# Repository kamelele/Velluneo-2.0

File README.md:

# Velluneo-2.0

[Projekt E27 z wymiennym wkładem LED](hardware/E27/README.md)

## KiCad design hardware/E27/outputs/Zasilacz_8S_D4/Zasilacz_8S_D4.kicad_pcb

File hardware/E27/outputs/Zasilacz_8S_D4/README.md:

# Velluneo E27 8S-D4

Open [Zasilacz_8S_D4.kicad_pro](Zasilacz_8S_D4.kicad_pro) in KiCad 10.0.8. This draft adds a hardware inhibit to the 8-LED supply while its 3.3 V logic rail is low. The [70 × 34 mm board](Zasilacz_8S_D4.kicad_pcb) is an unrouted placement study.

- [Schematic](Zasilacz_8S_D4.kicad_sch)
- [3D top](8S-D4-top.png) · [3D bottom](8S-D4-bottom.png)
- [Design decision and evidence](../../workflow/8s/driver-8s-d4-inhibit.md)

Retained fault state after full rail loss, independent insulation checks and routing remain open. The earlier [D3 study](../Zasilacz_8S_Draft/README.md) is available as a baseline.

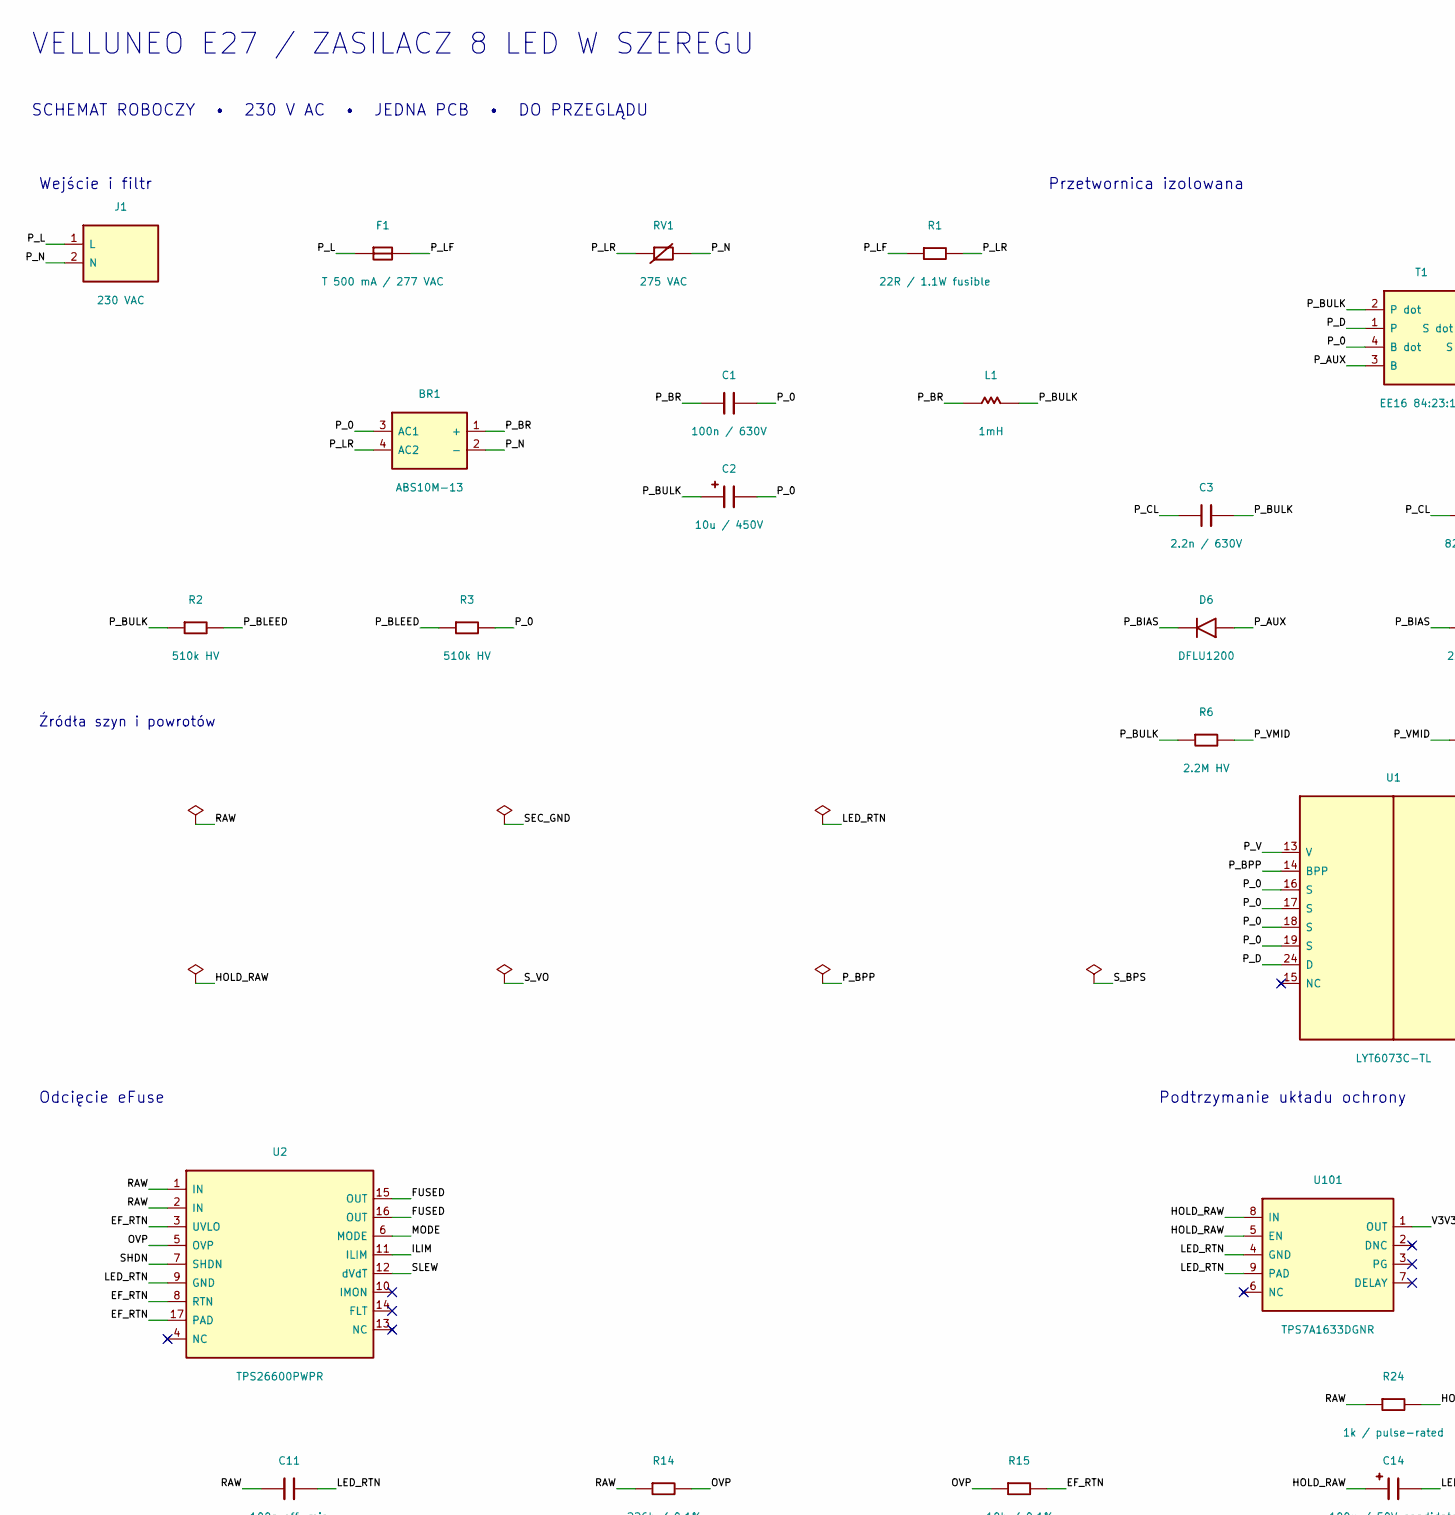
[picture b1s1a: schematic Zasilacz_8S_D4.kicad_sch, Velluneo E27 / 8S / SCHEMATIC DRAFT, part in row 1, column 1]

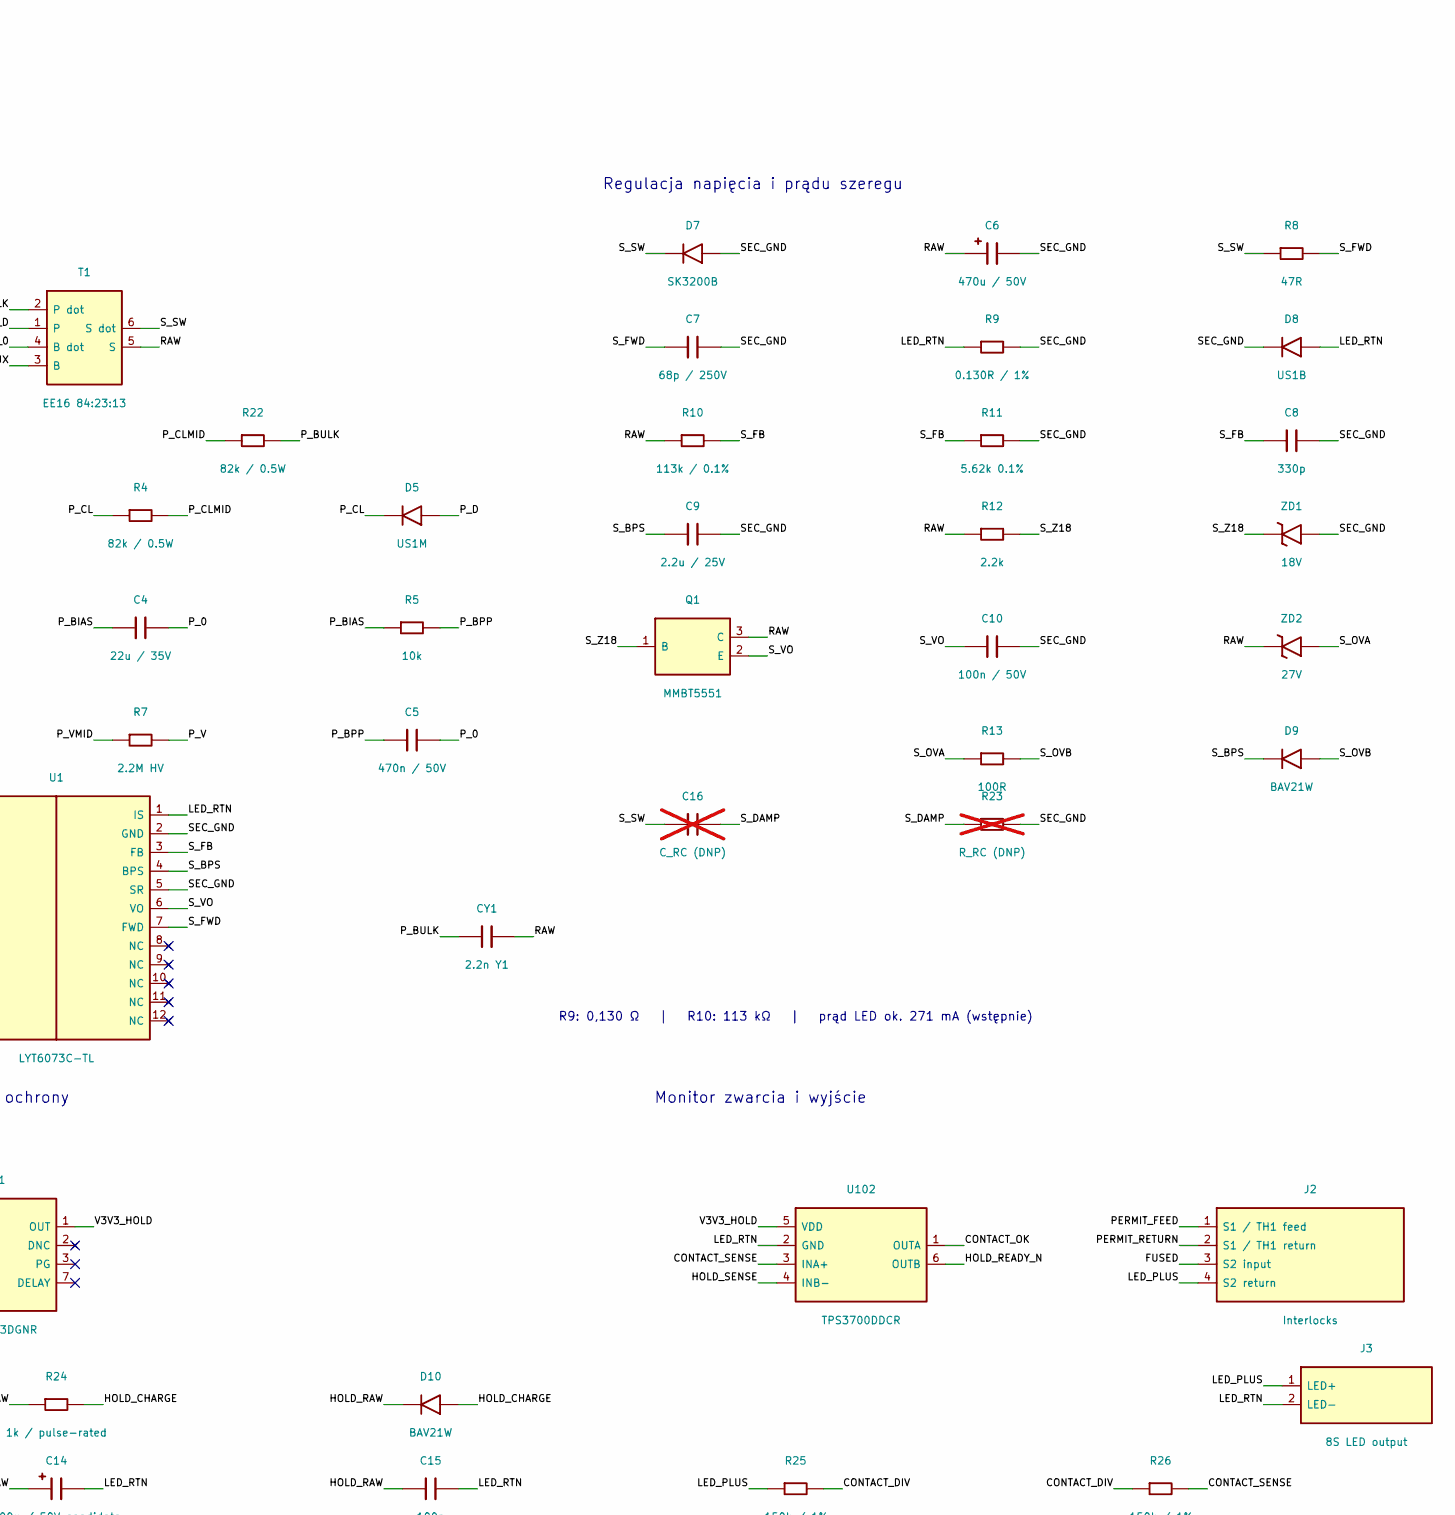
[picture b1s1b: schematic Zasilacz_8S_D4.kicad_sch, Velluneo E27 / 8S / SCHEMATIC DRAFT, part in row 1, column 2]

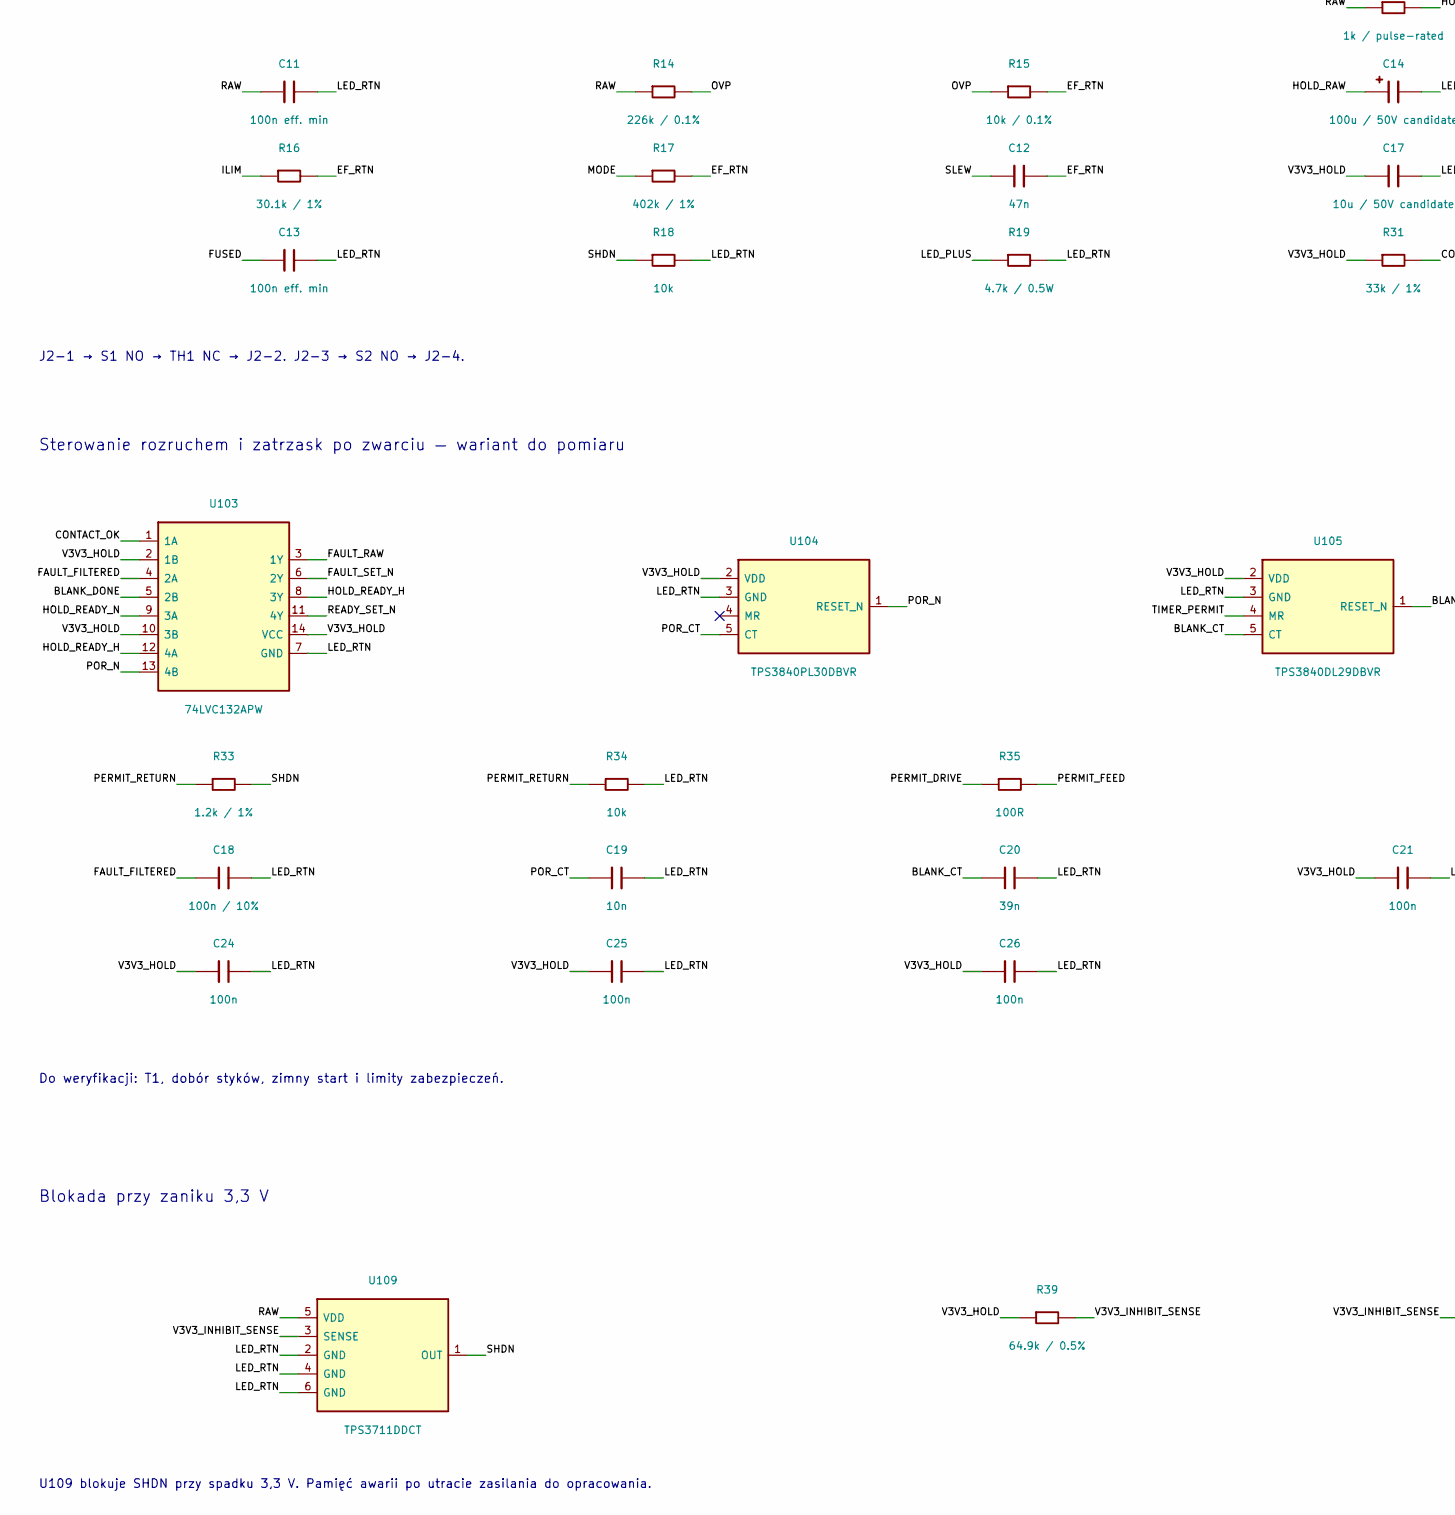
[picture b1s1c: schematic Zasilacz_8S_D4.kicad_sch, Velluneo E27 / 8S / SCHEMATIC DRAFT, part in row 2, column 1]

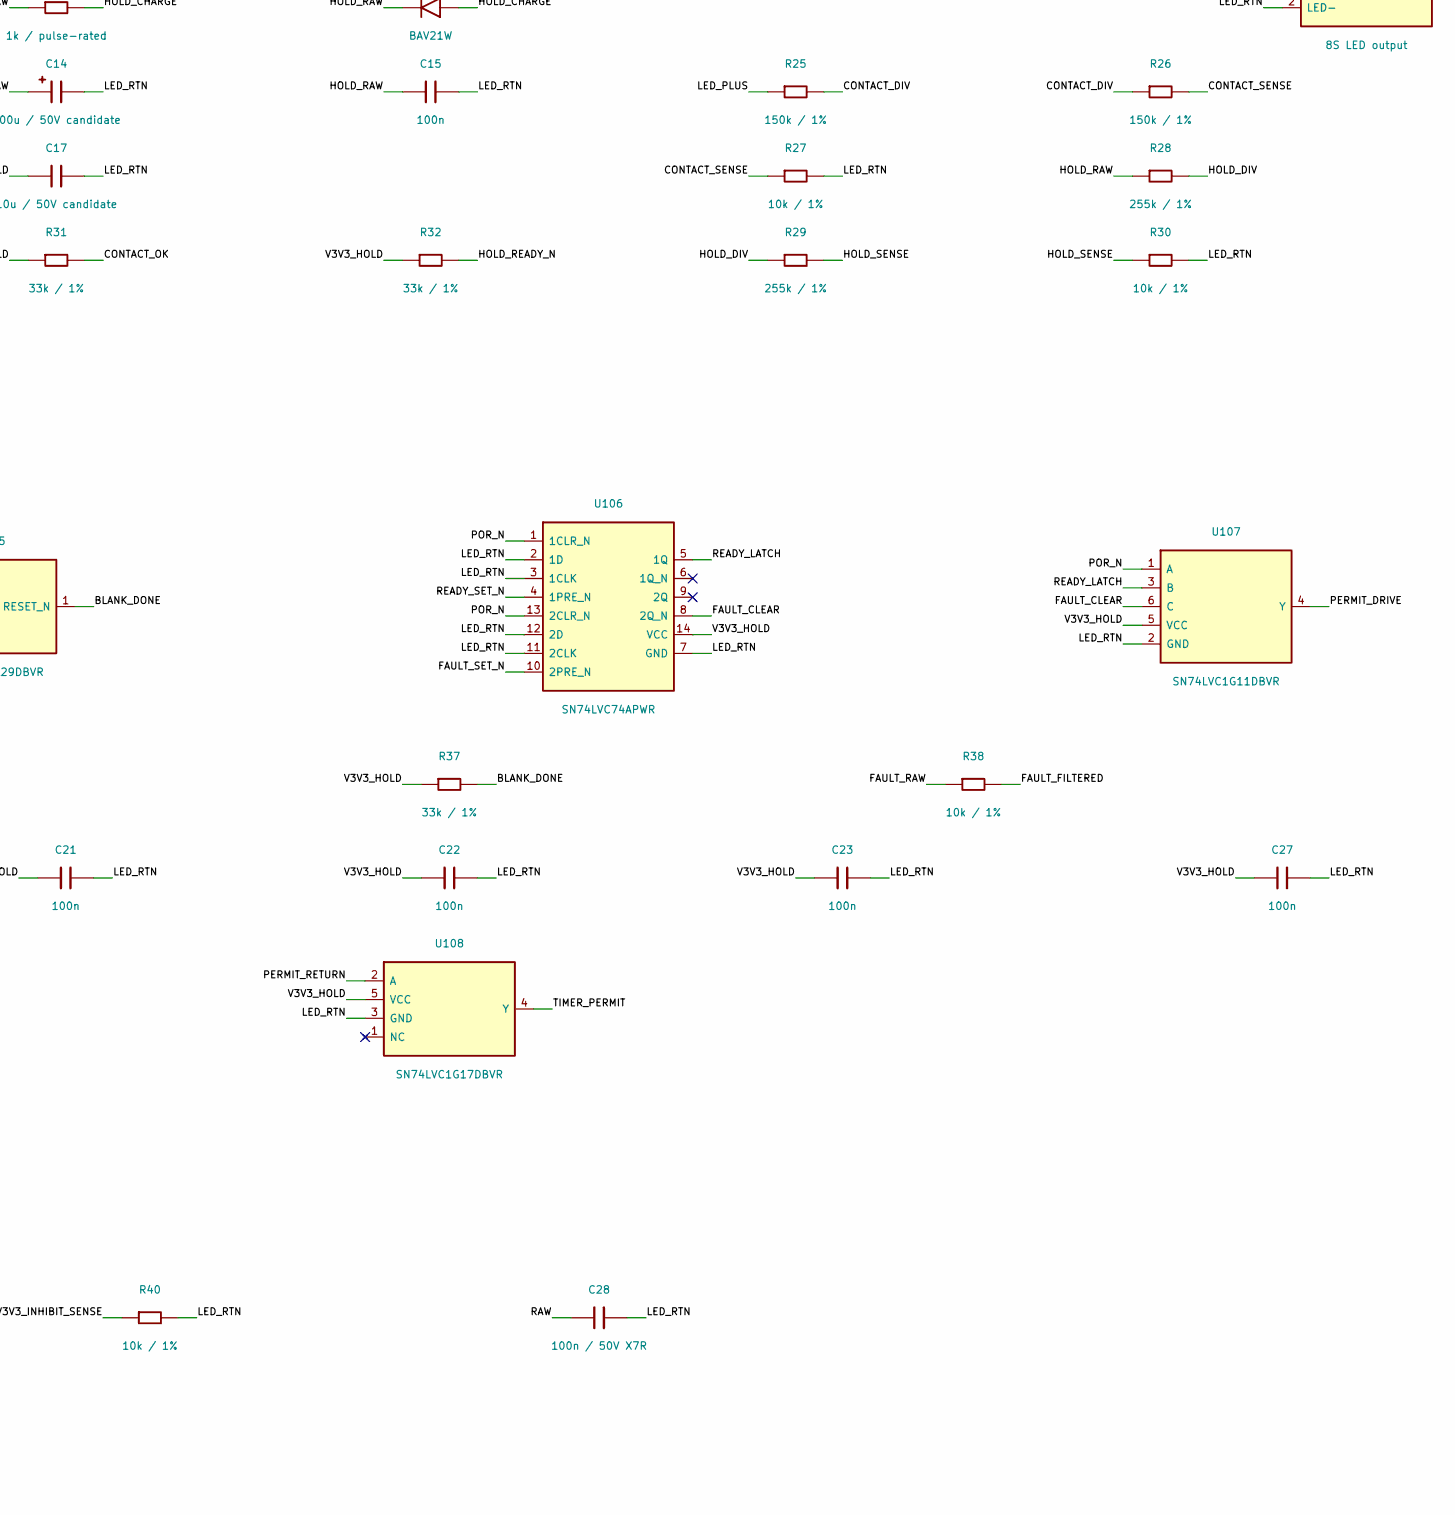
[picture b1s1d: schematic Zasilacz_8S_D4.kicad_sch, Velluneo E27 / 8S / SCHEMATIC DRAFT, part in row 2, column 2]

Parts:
BR1: ABS10M-13; ABS10M_SOPA-4_WX
C1: 100n / 630V; C_1210_3225Metric
C2: 10u / 450V; CP_Radial_D10.0mm_P5.00mm
C3: 2.2n / 630V; C_1206_3216Metric
C4: 22u / 35V; C_1206_3216Metric
C5: 470n / 50V; C_0805_2012Metric
C6: 470u / 50V; UCM_12p5
C7: 68p / 250V; C_0603_1608Metric
C8: 330p; C_0603_1608Metric
C9: 2.2u / 25V; C_1206_3216Metric
C10: 100n / 50V; C_0805_2012Metric
C11, C13: 100n eff. min; C_0805_2012Metric
C12: 47n; C_0603_1608Metric
C14: 100u / 50V candidate; CP_Elec_10x10.5
C15: 100n; C_0805_2012Metric
C16: C_RC (DNP); C_RC_1206_Hand; not fitted
C17: 10u / 50V candidate; C_1210_3225Metric
C18: 100n / 10%; C_0603_1608Metric
C19: 10n; C_0603_1608Metric
C20: 39n; C_0603_1608Metric
C21, C22, C23, C24, C25, C26, C27: 100n; C_0603_1608Metric
C28: 100n / 50V X7R; C_0805_2012Metric
CY1: 2.2n Y1; CY1_10mm
D5: US1M; D_SMA
D6: DFLU1200; D_PowerDI-123
D7: SK3200B; D_SMB
D8: US1B; D_SMA
D9, D10: BAV21W; D_SOD-123
F1: T 500 mA / 277 VAC; Schurter_UMT_H
J1: 230 VAC; Mains_L_N
J2: Interlocks; JST_GH_SM04B-GHS-TB_1x04-1MP_P1.25mm_Horizontal
J3: 8S LED output; JST_GH_SM02B-GHS-TB_1x02-1MP_P1.25mm_Horizontal
L1: 1mH; Wurth_TI_HV_8
Q1: MMBT5551; SOT-23
R1: 22R / 1.1W fusible; AC01_CS_WSZ
R2, R3: 510k HV; R_2010_5025Metric
R4, R22: 82k / 0.5W; R_1206_3216Metric
R5: 10k; R_0805_2012Metric
R6, R7: 2.2M HV; R_2010_5025Metric
R8: 47R; R_0805_2012Metric
R9: 0.130R / 1%; R_1206_3216Metric
R10: 113k / 0.1%; R_0603_1608Metric
R11: 5.62k 0.1%; R_0603_1608Metric
R12: 2.2k; R_0805_2012Metric
R13: 100R; R_0805_2012Metric
R14: 226k / 0.1%; R_0603_1608Metric
R15: 10k / 0.1%; R_0603_1608Metric
R16: 30.1k / 1%; R_0603_1608Metric
R17: 402k / 1%; R_0603_1608Metric
R18, R34: 10k; R_0603_1608Metric
R19: 4.7k / 0.5W; R_1206_3216Metric
R23: R_RC (DNP); R_RC_0805_Hand; not fitted
R24: 1k / pulse-rated; R_1206_3216Metric
R25, R26: 150k / 1%; R_0603_1608Metric
R27, R30, R38, R40: 10k / 1%; R_0603_1608Metric
R28, R29: 255k / 1%; R_0603_1608Metric
R31, R32, R37: 33k / 1%; R_0603_1608Metric
R33: 1.2k / 1%; R_0603_1608Metric
R35: 100R; R_0603_1608Metric
R39: 64.9k / 0.5%; R_0603_1608Metric
RV1: 275 VAC; TMOV14
T1: EE16 84:23:13; EE16_6pins_RFQ
U1: LYT6073C-TL; InSOP_24D
U2: TPS26600PWPR; PWP0016A
U101: TPS7A1633DGNR; TPS7A16_DGN
U102: TPS3700DDCR; SOT-23-6
U103: 74LVC132APW; TSSOP-14_4.4x5mm_P0.65mm
U104: TPS3840PL30DBVR; SOT-23-5
U105: TPS3840DL29DBVR; SOT-23-5
U106: SN74LVC74APWR; TSSOP-14_4.4x5mm_P0.65mm
U107: SN74LVC1G11DBVR; SOT-23-6
U108: SN74LVC1G17DBVR; SOT-23-5
U109: TPS3711DDCT; SOT-23-6
ZD1: 18V; D_SOD-123
ZD2: 27V; D_SOD-123

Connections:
/BLANK_CT: C20.1, U105.5 (CT)
/BLANK_DONE: R37.2, U103.5 (2B), U105.1 (RESET_N)
/CONTACT_DIV: R25.2, R26.1
/CONTACT_OK: R31.2, U102.1 (OUTA), U103.1 (1A)
/CONTACT_SENSE: R26.2, R27.1, U102.3 (INA+)
/EF_RTN: C12.2, R15.2, R16.2, R17.2, U2.3 (UVLO), U2.8 (RTN), U2.17 (PAD)
/FAULT_CLEAR: U106.8 (2Q_N), U107.6 (C)
/FAULT_FILTERED: C18.1, R38.2, U103.4 (2A)
/FAULT_RAW: R38.1, U103.3 (1Y)
/FAULT_SET_N: U103.6 (2Y), U106.10 (2PRE_N)
/FUSED: C13.1, J2.3 (S2 input), U2.15 (OUT), U2.16 (OUT)
/HOLD_CHARGE: D10.2 (A), R24.2
/HOLD_DIV: R28.2, R29.1
/HOLD_RAW: C14.1, C15.1, D10.1 (K), R28.1, U101.5 (EN), U101.8 (IN)
/HOLD_READY_H: U103.8 (3Y), U103.12 (4A)
/HOLD_READY_N: R32.2, U102.6 (OUTB), U103.9 (3A)
/HOLD_SENSE: R29.2, R30.1, U102.4 (INB-)
/ILIM: R16.1, U2.11 (ILIM)
/LED_PLUS: J2.4 (S2 return), J3.1 (LED+), R19.1, R25.1
/LED_RTN: C11.2, C13.2, C14.2, C15.2, C17.2, C18.2, C19.2, C20.2, C21.2, C22.2, C23.2, C24.2, C25.2, C26.2, C27.2, C28.2, D8.2 (A), J3.2 (LED-), R9.1, R18.2, R19.2, R27.2, R30.2, R34.2, R40.2, U1.1 (IS), U2.9 (GND), U101.4 (GND), U101.9 (PAD), U102.2 (GND), U103.7 (GND), U104.3 (GND), U105.3 (GND), U106.2 (1D), U106.3 (1CLK), U106.7 (GND), U106.11 (2CLK), U106.12 (2D), U107.2 (GND), U108.3 (GND), U109.2 (GND), U109.4 (GND), U109.6 (GND)
/MODE: R17.1, U2.6 (MODE)
/OVP: R14.2, R15.1, U2.5 (OVP)
/PERMIT_DRIVE: R35.1, U107.4 (Y)
/PERMIT_FEED: J2.1 (S1 / TH1 feed), R35.2
/PERMIT_RETURN: J2.2 (S1 / TH1 return), R33.1, R34.1, U108.2 (A)
/POR_CT: C19.1, U104.5 (CT)
/POR_N: U103.13 (4B), U104.1 (RESET_N), U106.1 (1CLR_N), U106.13 (2CLR_N), U107.1 (A)
/P_0: BR1.3 (AC1), C1.2, C2.2, C4.2, C5.2, R3.2, T1.4 (B dot), U1.16 (S), U1.17 (S), U1.18 (S), U1.19 (S)
/P_AUX: D6.2 (A), T1.3 (B)
/P_BIAS: C4.1, D6.1 (K), R5.1
/P_BLEED: R2.2, R3.1
/P_BPP: C5.1, R5.2, U1.14 (BPP)
/P_BR: BR1.1 (+), C1.1, L1.1
/P_BULK: C2.1, C3.2, CY1.1, L1.2, R2.1, R6.1, R22.2, T1.2 (P dot)
/P_CL: C3.1, D5.1 (K), R4.1
/P_CLMID: R4.2, R22.1
/P_D: D5.2 (A), T1.1, U1.24 (D)
/P_L: F1.1, J1.1 (L)
/P_LF: F1.2, R1.1
/P_LR: BR1.4 (AC2), R1.2, RV1.1
/P_N: BR1.2 (-), J1.2 (N), RV1.2
/P_V: R7.2, U1.13 (V)
/P_VMID: R6.2, R7.1
/RAW: C6.1, C11.1, C28.1, CY1.2, Q1.3 (C), R10.1, R12.1, R14.1, R24.1, T1.5 (S), U2.1 (IN), U2.2 (IN), U109.5 (VDD), ZD2.1 (K)
/READY_LATCH: U106.5 (1Q), U107.3 (B)
/READY_SET_N: U103.11 (4Y), U106.4 (1PRE_N)
/SEC_GND: C6.2, C7.2, C8.2, C9.2, C10.2, D7.2 (A), D8.1 (K), R9.2, R11.2, R23.2, U1.2 (GND), U1.5 (SR), ZD1.2 (A)
/SHDN: R18.1, R33.2, U2.7 (SHDN), U109.1 (OUT)
/SLEW: C12.1, U2.12 (dVdT)
/S_BPS: C9.1, D9.1 (K), U1.4 (BPS)
/S_DAMP: C16.2, R23.1
/S_FB: C8.1, R10.2, R11.1, U1.3 (FB)
/S_FWD: C7.1, R8.2, U1.7 (FWD)
/S_OVA: R13.1, ZD2.2 (A)
/S_OVB: D9.2 (A), R13.2
/S_SW: C16.1, D7.1 (K), R8.1, T1.6 (S dot)
/S_VO: C10.1, Q1.2 (E), U1.6 (VO)
/S_Z18: Q1.1 (B), R12.2, ZD1.1 (K)
/TIMER_PERMIT: U105.4 (MR), U108.4 (Y)
/V3V3_HOLD: C17.1, C21.1, C22.1, C23.1, C24.1, C25.1, C26.1, C27.1, R31.1, R32.1, R37.1, R39.1, U101.1 (OUT), U102.5 (VDD), U103.2 (1B), U103.10 (3B), U103.14 (VCC), U104.2 (VDD), U105.2 (VDD), U106.14 (VCC), U107.5 (VCC), U108.5 (VCC)
/V3V3_INHIBIT_SENSE: R39.2, R40.1, U109.3 (SENSE)

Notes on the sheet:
VELLUNEO E27 / ZASILACZ 8 LED W SZEREGU
SCHEMAT ROBOCZY • 230 V AC • JEDNA PCB • DO PRZEGLĄDU
Wejście i filtr
Przetwornica izolowana
Regulacja napięcia i prądu szeregu
R9: 0,130 Ω | R10: 113 kΩ | prąd LED ok. 271 mA (wstępnie)
Źródła szyn i powrotów
Odcięcie eFuse
Podtrzymanie układu ochrony
Monitor zwarcia i wyjście
J2-1 → S1 NO → TH1 NC → J2-2. J2-3 → S2 NO → J2-4.
Sterowanie rozruchem i zatrzask po zwarciu — wariant do pomiaru
Do weryfikacji: T1, dobór styków, zimny start i limity zabezpieczeń.
Blokada przy zaniku 3,3 V
U109 blokuje SHDN przy spadku 3,3 V. Pamięć awarii po utracie zasilania do opracowania.

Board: 2 copper layers, 94 parts (57 on the bottom side), 61 nets, no tracks yet.

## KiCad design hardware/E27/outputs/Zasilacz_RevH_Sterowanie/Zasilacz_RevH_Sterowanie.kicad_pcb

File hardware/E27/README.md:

# Velluneo E27

Żarówka E27 230 V z wymiennym wkładem Ø30 mm. Trzy wersje barwy (2700 K, 4000 K i 6500 K) korzystają z tego samego interfejsu i mechanizmu.

- **Zasilacz dzielony · wariant prototypowy** · [moc Rev K 55,5 × 34 mm](outputs/Zasilacz_RevK_Moc/README.md) · [sterowanie Rev H 30 × 25 mm](outputs/Zasilacz_RevH_Sterowanie/README.md) · [wspólny podgląd](outputs/Zasilacz_RevK_Moc/Podglady/Zasilacz_RevK_RevH_razem.png) · [pakiet JLCPCB](Pakiet_prototypu_JLCPCB.md)
- **Zasilacz dzielony · wariant archiwalny do oceny** · [moc Rev H 55,5 × 34 mm](outputs/Zasilacz_RevH_Moc/README.md) · [sterowanie Rev G 30 × 25 mm](outputs/Zasilacz_RevG_Sterowanie/README.md)
- [Studium Rev L · kompletne trasowanie valley-fill na czterech warstwach](outputs/Studium_RevL_ValleyFill/README.md)
- [Studium Rev J · korekcja harmonicznych i rozmieszczenie valley-fill](outputs/Studium_RevJ_ValleyFill/README.md)
- **Zasilacz dzielony Rev G** · [moc Rev G 55,5 × 34 mm](outputs/Zasilacz_RevG_Moc/README.md) · [sterowanie Rev G 30 × 25 mm](outputs/Zasilacz_RevG_Sterowanie/README.md) · [wspólny podgląd](outputs/Zasilacz_RevG_Moc/Podglady/Zasilacz_RevG_razem.png)
- **Zasilacz dzielony Rev F** · [płytka mocy 55,5 × 34 mm](outputs/Zasilacz_RevF_Moc/README.md) · [sterowanie 30 × 25 mm](outputs/Zasilacz_RevF_Sterowanie/README.md) · pliki do wyceny technologicznej JLCPCB
- [Zasilacz Rev E · mniejsza płytka, wariant dzielony i podglądy 3D](outputs/Studium_RevE/README.md)
- [Zasilacz Rev D · jedna płytka do wyceny w JLCPCB](outputs/Zasilacz_RevD_JLCPCB/README.md)
- [Zasilacz Rev B1 · odprowadzanie ciepła przez PCB](outputs/Zasilacz_RevB1/README.md) · [weryfikacja KiCad](outputs/Zasilacz_RevB1/Weryfikacja_KiCad_RevB1.md)
- [Zasilacz Rev B2 · moduł prób ochrony zwarciowej](outputs/Zasilacz_RevB2_Ochrona/README.md) · [wyniki modelu](outputs/Zasilacz_RevB2_Ochrona/Model_RevB2_przypadki.csv)
- [Rewizja B zasilacza i wyniki weryfikacji](outputs/Raport_E27_RevB.md) · [projekt KiCad](outputs/Zasilacz_RevB) · [BOM](outputs/BOM_Zasilacz_RevB.csv)
- [Projekt wkładu LED](outputs/Wklad_LED) · [mechanizm wymiany](outputs/Mechanizm_E27_RevA.svg)
- [Pakiet KiCad Rev B](outputs/E27_RevB_pakiet_KiCad.zip) · [plan prób](outputs/Plan_prob_RevB.md)
- [Dokumentacja rewizji A](outputs/Raport_E27_RevA.md) · [pakiet Rev A](outputs/E27_RevA_pakiet_KiCad.zip)
- [Studium Rev C](outputs/Studium_RevC/README.md) · [model mechaniczny KiCad](outputs/Studium_RevC/E27_RevC_Gabaryty.kicad_pcb) · [specyfikacja próbek transformatora EFD20](outputs/Studium_RevC/RFQ_T1_EFD20.md)

Rewizje zasilacza są dokumentacją rozwojową. Audyt wykazał błąd składni reguł odstępu w historycznych projektach mocy. Ich wyniki DRC mają wartość archiwalną. Pakiet mocy Rev H wstrzymano do zamówienia. [Wyniki ponownej kontroli](outputs/Zasilacz_RevH_Moc/Weryfikacja_RevH.md). Pliki oznaczone `Produkcja_DO_PRZEGLADU` służą do przeglądu technologicznego. Przed próbami z siecią konieczny jest przegląd transformatora, ochrony, izolacji kompletnego zespołu oraz stanowiska.

Skrypty w katalogu [work](work) uruchamia się z katalogu `hardware/E27` z KiCad 10.0.8. Regeneracja zmienia pliki w `outputs`. Na Windows skrypty zakładają standardową ścieżkę instalacji KiCad.

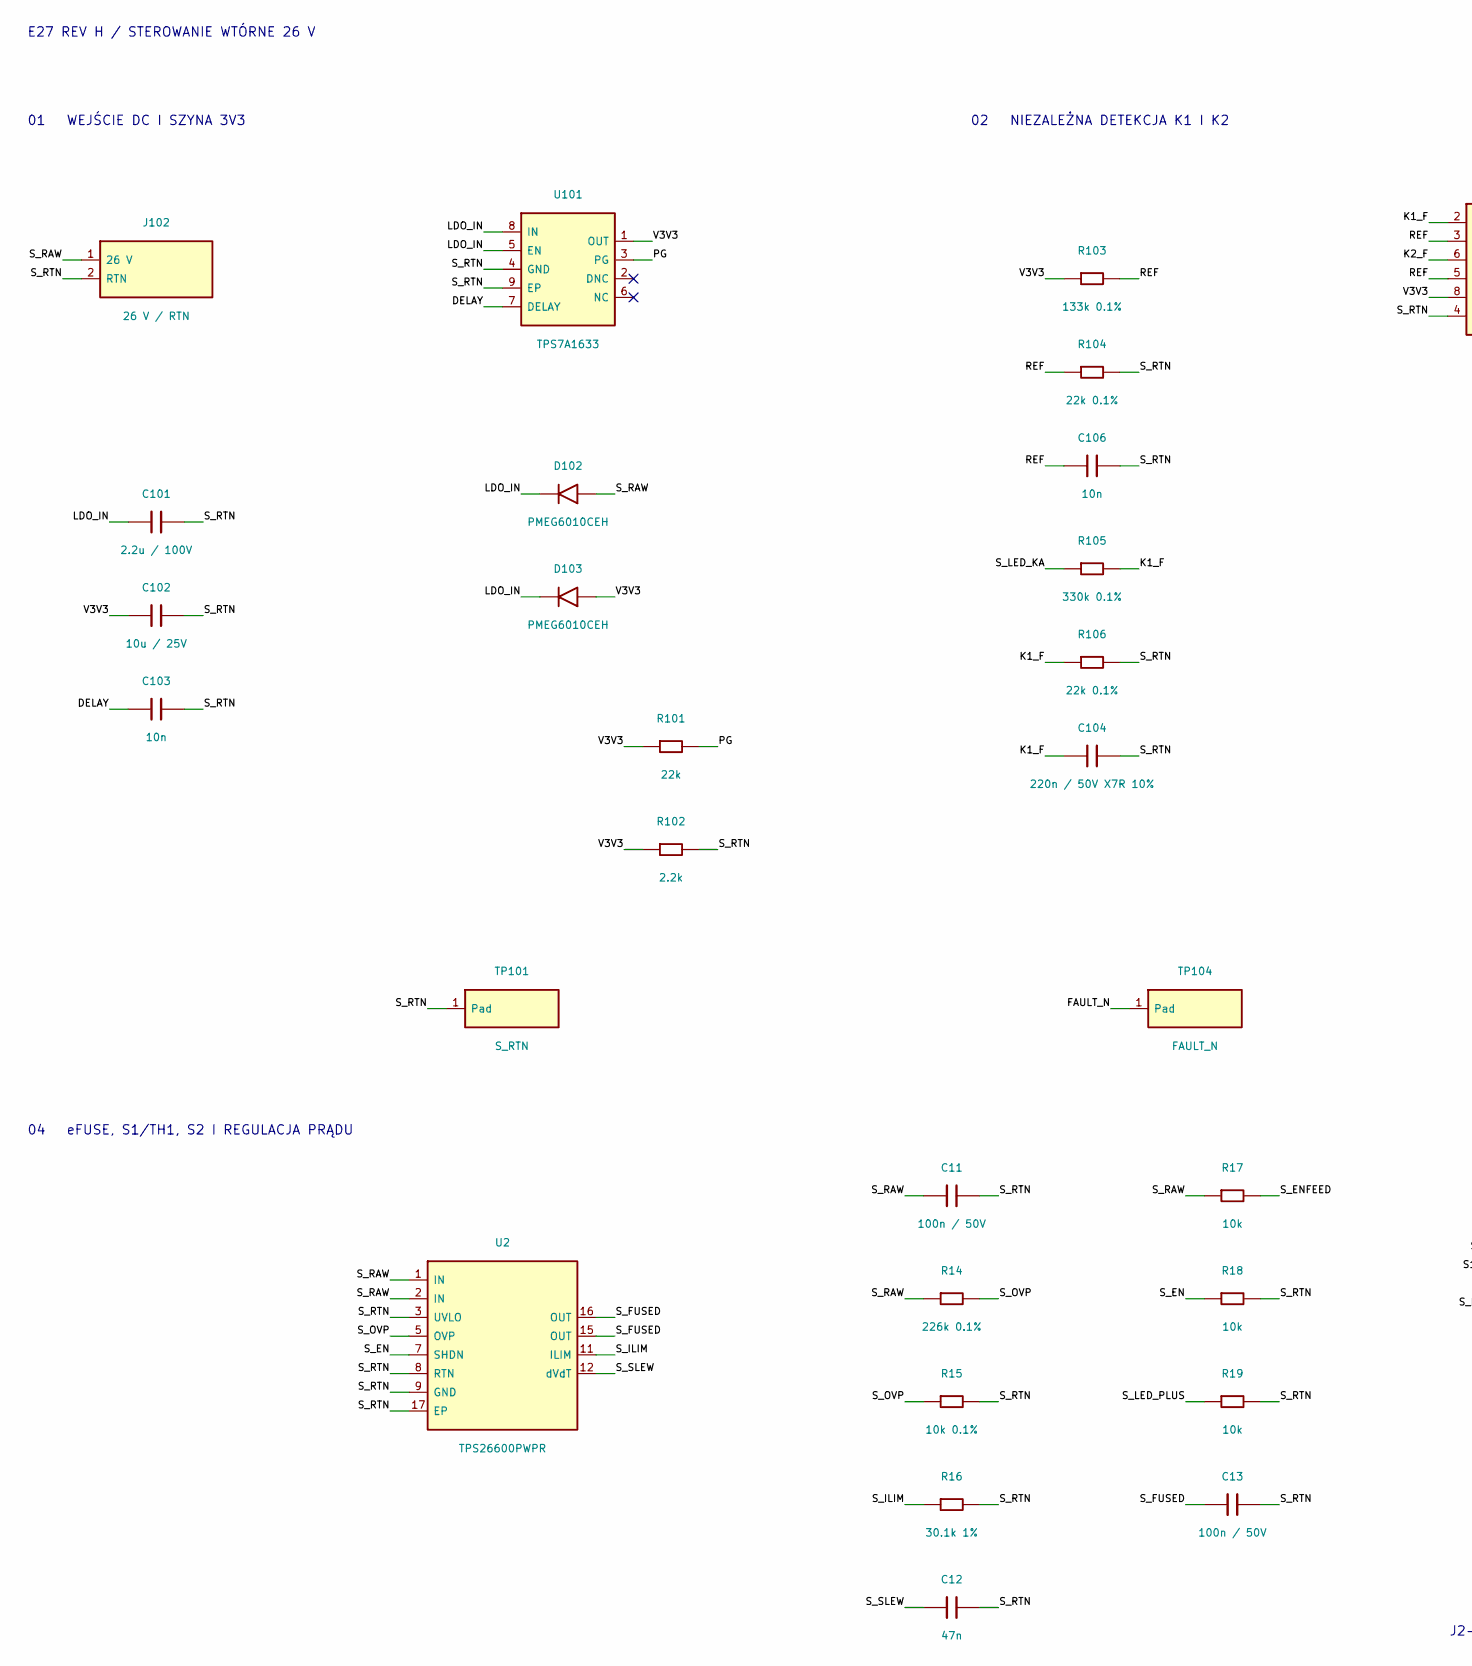
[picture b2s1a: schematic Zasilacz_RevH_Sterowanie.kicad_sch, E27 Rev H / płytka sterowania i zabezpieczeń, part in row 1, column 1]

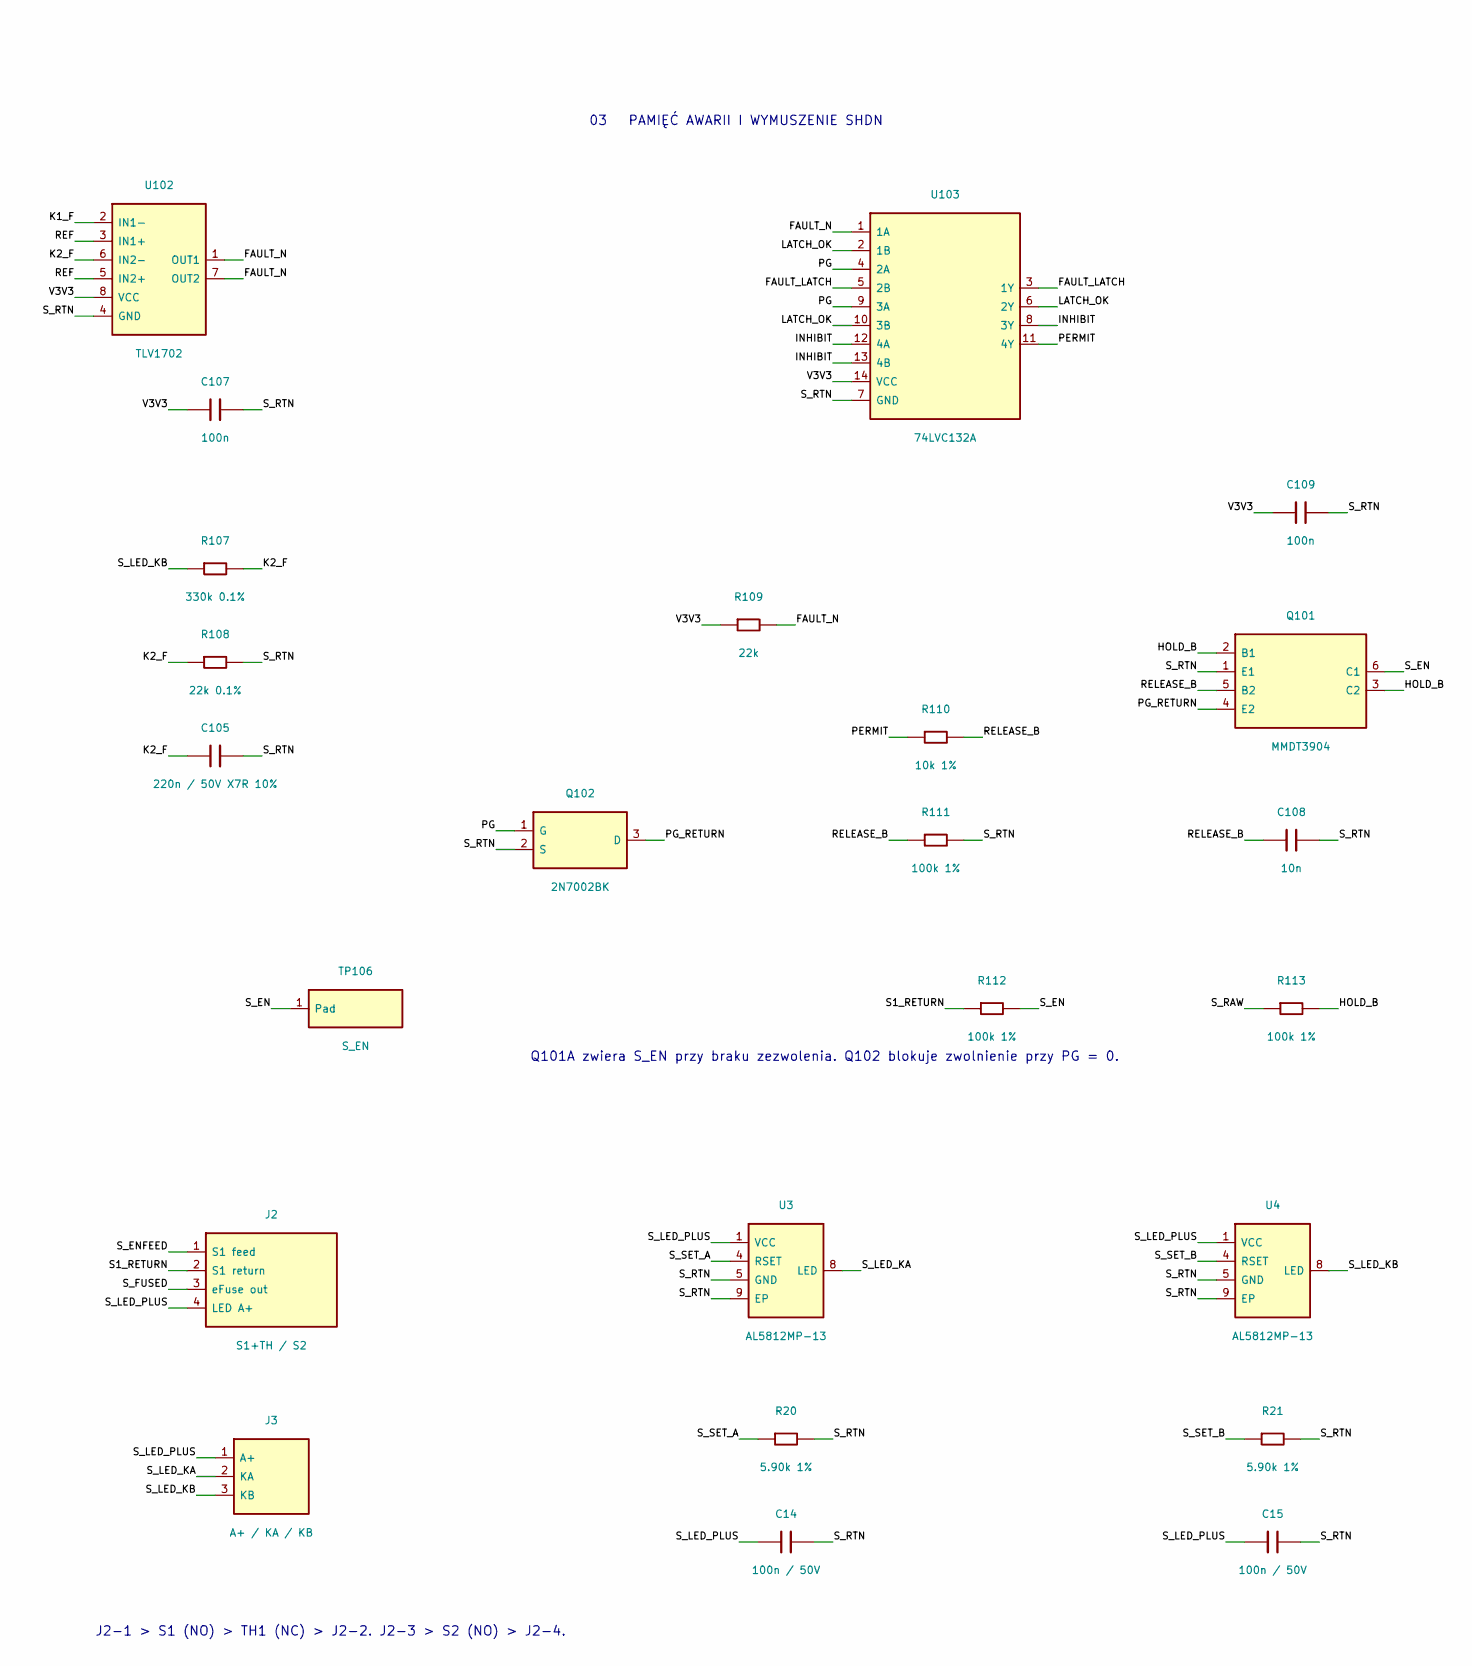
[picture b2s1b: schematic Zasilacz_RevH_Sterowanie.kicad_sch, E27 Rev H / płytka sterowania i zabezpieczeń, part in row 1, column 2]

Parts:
C11, C13, C14, C15: 100n / 50V; C_0805_2012Metric
C12: 47n; C_0603_1608Metric
C101: 2.2u / 100V; C_1210_3225Metric
C102: 10u / 25V; C_0805_2012Metric
C103, C106, C108: 10n; C_0603_1608Metric
C104, C105: 220n / 50V X7R 10%; C_0603_1608Metric
C107, C109: 100n; C_0603_1608Metric
D102, D103: PMEG6010CEH; D_SOD-123F
J2: S1+TH / S2; Harness_4pos
J3: A+ / KA / KB; Harness_3pos
J102: 26 V / RTN; Harness_26V_RTN
Q101: MMDT3904; SOT-363_SC-70-6
Q102: 2N7002BK; SOT-23
R14: 226k 0.1%; R_0603_1608Metric
R15: 10k 0.1%; R_0603_1608Metric
R16: 30.1k 1%; R_0603_1608Metric
R17, R18: 10k; R_0603_1608Metric
R19: 10k; R_0805_2012Metric
R20, R21: 5.90k 1%; R_0603_1608Metric
R101, R109: 22k; R_0603_1608Metric
R102: 2.2k; R_0603_1608Metric
R103: 133k 0.1%; R_0603_1608Metric
R104, R106, R108: 22k 0.1%; R_0603_1608Metric
R105, R107: 330k 0.1%; R_0603_1608Metric
R110: 10k 1%; R_0603_1608Metric
R111, R112, R113: 100k 1%; R_0603_1608Metric
TP101: S_RTN; TestPoint_Pad_D1.5mm
TP104: FAULT_N; TestPoint_Pad_D1.5mm
TP106: S_EN; TestPoint_Pad_D1.5mm
U2: TPS26600PWPR; PWP0016A
U3, U4: AL5812MP-13; E27_Al5812_MSOP
U101: TPS7A1633; TPS7A16_DGN
U102: TLV1702; MSOP-8_3x3mm_P0.65mm
U103: 74LVC132A; TSSOP-14_4.4x5mm_P0.65mm

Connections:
/DELAY: C103.1, U101.7 (DELAY)
/FAULT_LATCH: U103.3 (1Y), U103.5 (2B)
/FAULT_N: R109.2, TP104.1, U102.1 (OUT1), U102.7 (OUT2), U103.1 (1A)
/HOLD_B: Q101.2 (B1), Q101.3 (C2), R113.2
/INHIBIT: U103.8 (3Y), U103.12 (4A), U103.13 (4B)
/K1_F: C104.1, R105.2, R106.1, U102.2 (IN1-)
/K2_F: C105.1, R107.2, R108.1, U102.6 (IN2-)
/LATCH_OK: U103.2 (1B), U103.6 (2Y), U103.10 (3B)
/LDO_IN: C101.1, D102.1 (K), D103.1 (K), U101.5 (EN), U101.8 (IN)
/PERMIT: R110.1, U103.11 (4Y)
/PG: Q102.1 (G), R101.2, U101.3 (PG), U103.4 (2A), U103.9 (3A)
/PG_RETURN: Q101.4 (E2), Q102.3 (D)
/REF: C106.1, R103.2, R104.1, U102.3 (IN1+), U102.5 (IN2+)
/RELEASE_B: C108.1, Q101.5 (B2), R110.2, R111.1
/S1_RETURN: J2.2 (S1 return), R112.1
/S_EN: Q101.6 (C1), R18.1, R112.2, TP106.1, U2.7 (SHDN)
/S_ENFEED: J2.1 (S1 feed), R17.2
/S_FUSED: C13.1, J2.3 (eFuse out), U2.15 (OUT), U2.16 (OUT)
/S_ILIM: R16.1, U2.11 (ILIM)
/S_LED_KA: J3.2 (KA), R105.1, U3.8 (LED)
/S_LED_KB: J3.3 (KB), R107.1, U4.8 (LED)
/S_LED_PLUS: C14.1, C15.1, J2.4 (LED A+), J3.1 (A+), R19.1, U3.1 (VCC), U4.1 (VCC)
/S_OVP: R14.2, R15.1, U2.5 (OVP)
/S_RAW: C11.1, D102.2 (A), J102.1 (26 V), R14.1, R17.1, R113.1, U2.1 (IN), U2.2 (IN)
/S_RTN: C11.2, C12.2, C13.2, C14.2, C15.2, C101.2, C102.2, C103.2, C104.2, C105.2, C106.2, C107.2, C108.2, C109.2, J102.2 (RTN), Q101.1 (E1), Q102.2 (S), R15.2, R16.2, R18.2, R19.2, R20.2, R21.2, R102.2, R104.2, R106.2, R108.2, R111.2, TP101.1, U2.3 (UVLO), U2.8 (RTN), U2.9 (GND), U2.17 (EP), U3.5 (GND), U3.9 (EP), U4.5 (GND), U4.9 (EP), U101.4 (GND), U101.9 (EP), U102.4 (GND), U103.7 (GND)
/S_SET_A: R20.1, U3.4 (RSET)
/S_SET_B: R21.1, U4.4 (RSET)
/S_SLEW: C12.1, U2.12 (dVdT)
/V3V3: C102.1, C107.1, C109.1, D103.2 (A), R101.1, R102.1, R103.1, R109.1, U101.1 (OUT), U102.8 (VCC), U103.14 (VCC)

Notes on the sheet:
E27 REV H / STEROWANIE WTÓRNE 26 V
01 WEJŚCIE DC I SZYNA 3V3
02 NIEZALEŻNA DETEKCJA K1 I K2
03 PAMIĘĆ AWARII I WYMUSZENIE SHDN
04 eFUSE, S1/TH1, S2 I REGULACJA PRĄDU
J2-1 > S1 (NO) > TH1 (NC) > J2-2. J2-3 > S2 (NO) > J2-4.
Q101A zwiera S_EN przy braku zezwolenia. Q102 blokuje zwolnienie przy PG = 0.
